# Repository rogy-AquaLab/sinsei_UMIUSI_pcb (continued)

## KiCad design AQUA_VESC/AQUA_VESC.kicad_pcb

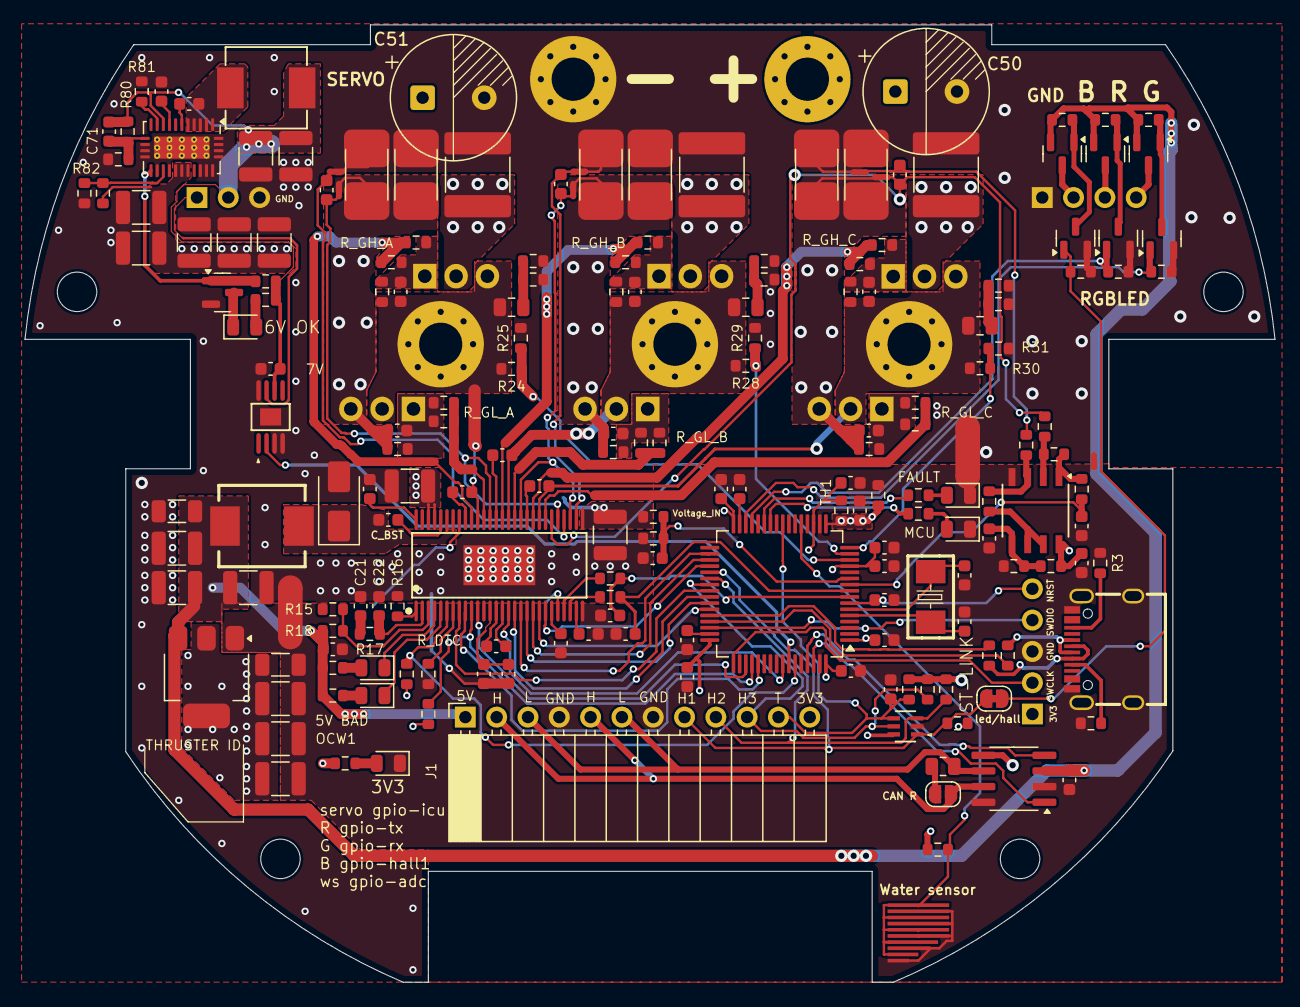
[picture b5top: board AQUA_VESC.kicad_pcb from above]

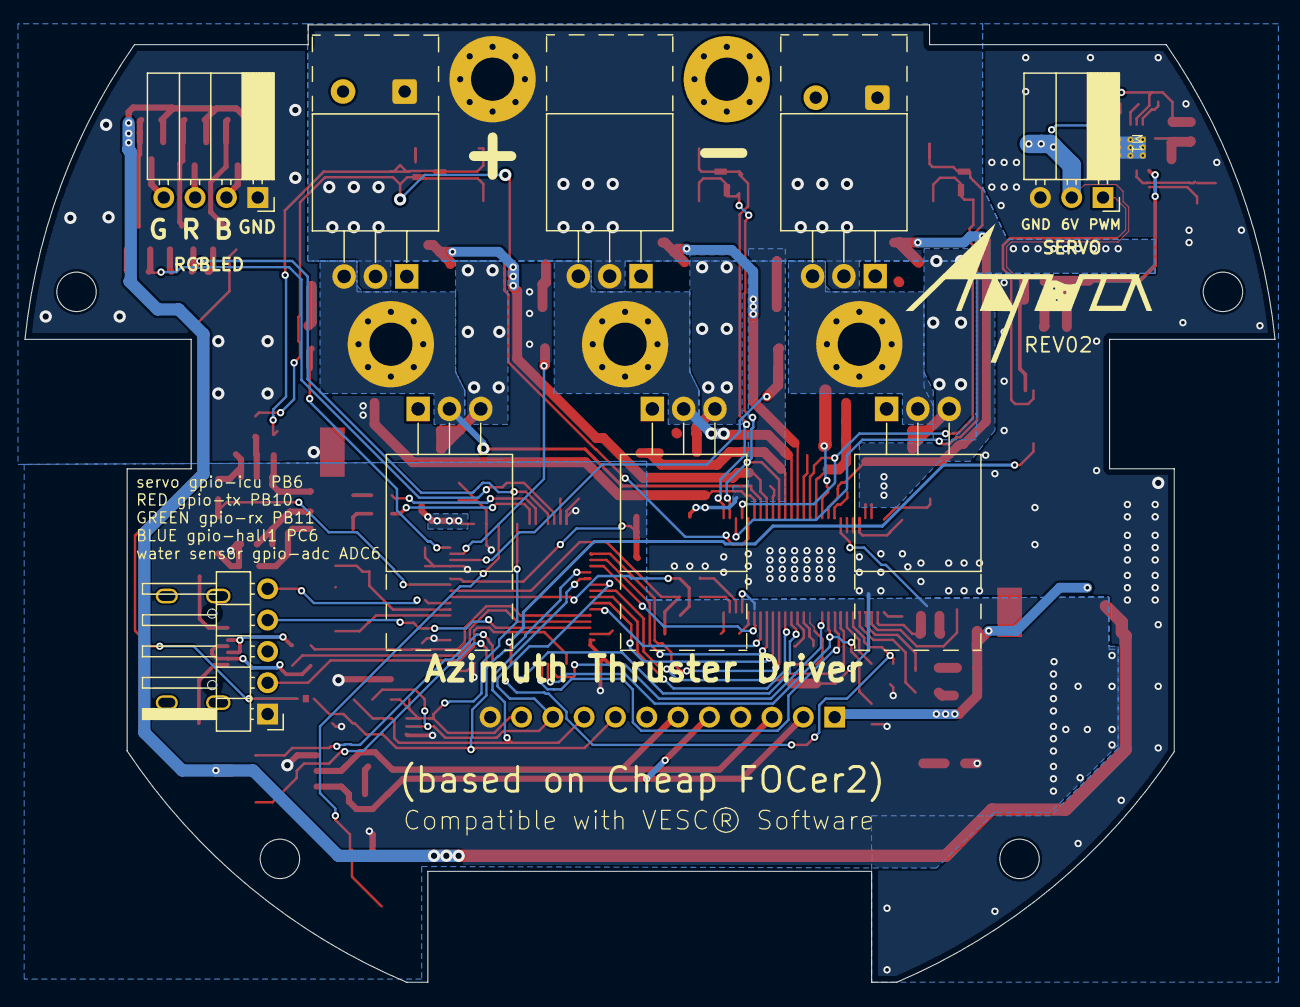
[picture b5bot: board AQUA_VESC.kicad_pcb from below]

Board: 2 copper layers, 101.4 x 77.7 mm, 213 parts (9 on the bottom side), 128 nets.

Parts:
5V1, 6V_OK1: YELLOW; LED_0805_2012Metric
C1, C2, C4, C5, C6, C7, C8, C10, C15, C16, C25, C44, C46: 100n; C_0603_1608Metric
C3: 4.7u; C_0603_1608Metric
C9, C62: 1u; C_0603_1608Metric
C11, C12: 15p; C_0603_1608Metric
C13, C14, C32, C33, C36, C41, C52, C72: 2.2u; C_0603_1608Metric
C17, C26: 2.2u; C_1206_3216Metric
C18, C19, C20, C27, C28, C29, C69, C70: 22u; C_1210_3225Metric
C21: 6.8n; C_0603_1608Metric
C22: 150p; C_0603_1608Metric
C23, C53, C54, C55, C59, C60, C61: 10n; C_0603_1608Metric
C24, C42, C63, C64, C65, C66, C67: 4.7u, 100V; C_1210_3225Metric
C30, C34, C35: 220n; C_0603_1608Metric
C31: 22n; C_0603_1608Metric
C37, C38, C39, C40, C43, C45: 1n; C_0603_1608Metric
C47, C48, C49: 10uF, 100V; C_2220_5750Metric
C50, C51: 330u; CP_Radial_D10.0mm_P5.00mm_nofill
C56, C57, C58: 4.7n, 100V; C_0805_2012Metric
C68: 0.47u; C_0603_1608Metric
C71: 12p; C_0603_1608Metric
D1: RED; LED_0805_2012Metric
D2: WHITE; LED_0805_2012Metric
D3: EMERALD; LED_0805_2012Metric
D4: SS210; D_SMA
H1, H6, H7, H8, H9: MountingHole_Pad; MountingHole_3.5mm_Pad_Via
H2, H3, H4, H5: MountingHole; MountingHole_3.2mm_M3
J1: Conn_01x12_Socket; PinSocket_1x12_P2.54mm_Horizontal
J2: Conn_01x05_Pin; PinHeader_1x05_P2.54mm_Horizontal
JP1: SolderJumper_2_Bridged; SolderJumper-2_P1.3mm_Bridged_RoundedPad1.0x1.5mm
JP2: SolderJumper_2_Open; SolderJumper-2_P1.3mm_Open_RoundedPad1.0x1.5mm
M1: Motor_Servo_Hitec; PinSocket_1x03_P2.54mm_Horizontal
NT1, NT2: NetTie_2; NetTie-2_SMD_Pad2.0mm
NT3, NT4, NT5, NT6, NT7, NT8, NT9: NetTie_2; NetTie-2_SMD_Pad0.5mm
OCW1: RED; LED_0805_2012Metric
Q1, Q2, Q3, Q4, Q5, Q6: TK3R2E06PL; TO-220-3_Horizontal_TabUp_no_hole
Q7, Q8, Q9: AO3401A; SOT-23
Q10, Q11, Q12, Q13: 2N7002; SOT-23
R1, R24, R28, R30: 39k; R_0603_1608Metric
R2, R7, R8, R9, R25, R29, R31: 2.2k; R_0603_1608Metric
R3, R6: 5.1k; R_0603_1608Metric
R4, R5: 22; R_0603_1608Metric
R10, R21, R22, R34, R37, R39, R70, R71, R72, R73, R74, R75: 10k; R_0603_1608Metric
R11, R77, R80: 100k; R_0603_1608Metric
R12, R13, R14: 100; R_0603_1608Metric
R15: 3.3k; R_0603_1608Metric
R16: 220k; R_0603_1608Metric
R17, R33, R38, R82: 20k; R_0603_1608Metric
R18: 18k; R_0603_1608Metric
R19, R20, R23, R26, R27, R32, R35, R36: 1k; R_0603_1608Metric
R40, R41, R42, R43, R44, R45, R49, R50, R51, R52, R53, R54, R55, R56, R57, R58, R59, R60: 10; R_0603_1608Metric
R46, R47, R48, R61, R62, R63: 4.7k; R_0603_1608Metric
R64, R65, R66, R67, R68, R69: 1mΩ; R_2512_Yageo_big_pads
R76: 390; R_0603_1608Metric
R78: 15k; R_0603_1608Metric
R79: 51k; R_0603_1608Metric
R81: 82k; R_0603_1608Metric
RGBLED1: Conn_01x04_Pin; PinSocket_1x04_P2.54mm_Horizontal
R_can_termination1: 120; R_0805_2012Metric
TH1: Thermistor_NTC; R_0603_1608Metric
U1: SMF05CT1G; SOT-363-6_2P2X1P35_ONS
U2: wetness sensor
U3: STM32F405RGTx; LQFP-64_10x10mm_P0.5mm
U4: TJA1051T-3; SOIC-8_3.9x4.9mm_P1.27mm
U5: AMS1117-3.3; SOT-223-3_TabPin2
U6: DRV8301QDCAQ1; HTSSOP-56_L14.0-W6.0-P0.50-LS8.0-BL
U7: 22uH; IND-SMD_L7.0-W6.6
U8: TP2604-SR; SO-8SOIC-8_TPK
U9: MX27524ES; EMSOP-8_L3.0-W3.0-P0.65-LS4.9-BL-EP
U10: 15uH; IND-SMD_L7.1-W6.6
U11: LM76002; Texas_RNP0030B_WQFN-30-1EP_4x6mm_P0.5mm_EP1.8x4.5mm_Thermal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
USB1: TYPEC; USB-C_SMD-TYPE-C-31-M-12
X1: 8MHz; CRYSTAL-SMD_L5.0-W3.2

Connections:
+3V3: C3.1, C4.1, C5.1, C6.1, C7.1, C8.1, C9.1, C17.1, C18.1, C19.1, C20.1, C44.1, J1.12, J2.1, R7.1, R8.1, R9.1, R10.1, R11.2, R14.1, R21.1, R23.1, R34.1, TH1.1, U1.6 (CATHODE), U3.1 (VBAT), U3.13 (VDDA), U3.19 (VDD), U3.32 (VDD), U3.48 (VDD), U3.64 (VDD), U4.5 (VIO), U5.2 (VO), U6.24 (REF), U6.49 (VDD_SPI), U8.8 (+VS)
+5V: C15.1, C16.1, C26.1, C27.1, C28.1, C29.1, J1.1, Q7.2 (S), Q8.2 (S), Q9.2 (S), R18.2, R19.1, R20.1, R70.2, R71.2, R72.2, U4.3 (VCC), U5.3 (VI), U7.2
+6V: C62.1, C69.1, C70.1, C71.2, M1.2 (+), R76.1, R79.1, R80.2, U9.6 (VCC), U10.2, U11.9 (BIAS)
/CAN/CANH: J1.2, J1.5, JP2.2 (B), U4.7 (CANH)
/CAN/CANL: J1.3, J1.6, R_can_termination1.2, U4.6 (CANL)
/CAN/CAN_RX: U3.61 (PB8), U4.4 (RXD)
/CAN/CAN_TX: U3.62 (PB9), U4.1 (TXD)
/DRV8301/BR_SO1: C38.1, R26.2, U3.8 (PC0)
/DRV8301/BR_SO2: C39.1, R27.2, U3.9 (PC1)
/DRV8301/BR_SO3: C43.1, R32.1, U3.10 (PC2)
/DRV8301/CS: U3.40 (PC9), U6.8 (*SCS)
/DRV8301/EN_GATE: U3.57 (PB5), U6.16 (EN_GATE)
/DRV8301/FAULT: R21.2, U3.59 (PB7), U6.6 (*FAULT)
/DRV8301/GH_A: R40.1, R43.1, U6.47 (GH_A)
/DRV8301/GH_B: R41.1, R44.1, U6.42 (GH_B)
/DRV8301/GH_C: R42.1, R45.1, U6.37 (GH_C)
/DRV8301/GL_A: R49.1, R52.1, U6.45 (GL_A)
/DRV8301/GL_B: R50.1, R53.1, U6.40 (GL_B)
/DRV8301/GL_C: R51.1, R54.1, U6.35 (GL_C)
/DRV8301/H1: U3.41 (PA8), U6.17 (INH_A)
/DRV8301/H1_LOW: C37.2, NT4.1, U6.33 (SN1), U6.44 (SL_A)
/DRV8301/H1_VS: C30.2, C53.2, C56.1, H7.1, Q1.3 (S), Q4.2 (D), R24.2, R46.2, U6.46 (SH_A)
/DRV8301/H2: U3.42 (PA9), U6.19 (INH_B)
/DRV8301/H2_LOW: C40.2, NT5.1, U6.31 (SN2), U6.39 (SL_B)
/DRV8301/H2_VS: C34.2, C54.2, C57.1, H8.1, Q2.3 (S), Q5.2 (D), R28.2, R47.2, U6.41 (SH_B)
/DRV8301/H3: U3.43 (PA10), U6.21 (INH_C)
/DRV8301/H3_LOW: C45.1, NT6.1, R35.1, U6.34 (SL_C)
/DRV8301/H3_VS: C35.2, C55.2, C58.1, H9.1, Q3.3 (S), Q6.2 (D), R30.2, R48.2, U6.36 (SH_C)
/DRV8301/L1: U3.34 (PB13), U6.18 (INL_A)
/DRV8301/L2: U3.35 (PB14), U6.20 (INL_B)
/DRV8301/L3: U3.36 (PB15), U6.22 (INL_C)
/DRV8301/SCLK: U3.51 (PC10), U6.11 (SCLK)
/DRV8301/SDI: U3.53 (PC12), U6.9 (SDI)
/DRV8301/SDO: R23.2, U3.52 (PC11), U6.10 (SDO)
/DRV8301/SENS1: R24.1, R25.1, U3.14 (PA0)
/DRV8301/SENS2: R28.1, R29.1, U3.15 (PA1)
/DRV8301/SENS3: R30.1, R31.1, U3.16 (PA2)
/DRV8301/SPA: C37.1, NT7.1, U6.32 (SP1)
/DRV8301/SPB: C40.1, NT8.1, U6.30 (SP2)
/DRV8301/SPC: C45.2, NT9.1, R36.1
/Power MOSFETs/TEMP: C52.1, R39.1, TH1.2, U3.17 (PA3)
/RGBLED_Driver/BLUE_OUT: Q9.3 (D), RGBLED1.2
/RGBLED_Driver/GREEN_GATE: Q11.1 (G), R74.1, U3.30 (PB11)
/RGBLED_Driver/GREEN_OUT: Q8.3 (D), RGBLED1.4
/RGBLED_Driver/RED_GATE: Q10.1 (G), R73.1, U3.29 (PB10)
/RGBLED_Driver/RED_OUT: Q7.3 (D), RGBLED1.3
/SERVO/SERVO_PWM: U3.58 (PB6), U9.2 (INA)
/STM32F405/ADC_EXT: R11.1, U2.1 (A), U3.21 (PA5)
/STM32F405/AN_IN: C1.1, R1.2, R2.1, U3.11 (PC3)
/STM32F405/HALL_1: J1.8, JP1.1 (A), R7.2, U1.1 (CATHODE), U3.37 (PC6)
/STM32F405/HALL_2: J1.9, R8.2, U1.3 (CATHODE), U3.38 (PC7)
/STM32F405/HALL_3: J1.10, R9.2, U1.5 (CATHODE), U3.39 (PC8)
/STM32F405/LED_GREEN: R13.1, U3.26 (PB0)
/STM32F405/LED_RED: R12.1, U3.27 (PB1)
/STM32F405/TEMP_MOTER: C2.1, J1.11, R10.2, U1.4 (CATHODE), U3.24 (PC4)
/STM32F405/USB_DM: R4.1, U3.44 (PA11)
/STM32F405/USB_DP: R5.1, U3.45 (PA12)
BLUE_GATE: JP1.2 (B), Q12.1 (G), R75.1
GNDD: C2.2, C3.2, C4.2, C5.2, C6.2, C7.2, C8.2, C9.2, C10.2, C11.2, C12.2, C13.2, C14.2, C15.2, C16.2, C17.2, C18.2, C19.2, C20.2, C36.1, C38.2, C39.2, C41.2, C43.2, C44.2, C46.2, C52.2, D1.1 (K), D2.1 (K), D3.1 (K), J1.4, J1.7, J2.3, NT1.1, NT2.1, NT3.1, R3.1, R6.2, R22.1, R37.2, R39.2, U1.2 (ANODE), U2.2 (B), U3.12 (VSSA), U3.18 (VSS), U3.60 (BOOT0), U3.63 (VSS), U4.2 (GND), U4.8 (S), U5.1 (GND), U6.28 (AGND), U8.4 (-VS), USB1.0 (SH), USB1.1 (SH), USB1.2 (SH), USB1.3 (SH), USB1.A1 (GND), USB1.A12 (GND), USB1.B1 (GND), USB1.B12 (GND)
GNDPWR: C1.2, C21.1, C22.1, C23.2, C24.2, C26.2, C27.2, C28.2, C29.2, C32.2, C33.2, C42.2, C47.2, C48.2, C49.2, C50.2, C51.2, C62.2, C63.2, C64.2, C65.2, C66.2, C67.2, C69.2, C70.2, C72.2, D4.2 (A), H6.1, M1.3 (-), NT1.2, NT2.2, NT3.2, NT7.2, NT8.2, NT9.2, Q10.2 (S), Q11.2 (S), Q12.2 (S), Q13.2 (S), R2.2, R15.1, R16.1, R25.2, R29.2, R31.2, R55.1, R56.1, R57.1, R58.1, R59.1, R60.1, R64.1, R65.1, R66.1, R67.1, R68.1, R69.1, R73.2, R74.2, R75.2, R78.2, R81.1, R82.2, RGBLED1.1, U6.57 (EPAD), U9.3 (GND), U9.4 (INB), U9.8 (ENB), U9.9 (EP), U11.13 (AGND), U11.14 (AGND), U11.15 (AGND), U11.17 (SYNC/MODE), U11.19 (NC_{GND}), U11.24 (PGND), U11.25 (PGND), U11.26 (PGND), U11.27 (NC_{GND}), U11.28 (NC_{GND}), U11.29 (NC_{GND}), U11.30 (NC_{GND}), U11.31 (AGND)
NRST: C10.1, J2.5, U3.7 (NRST)
unnamed: 5V1.2 (A), R19.2
unnamed: 5V1.1 (K), U6.4 (PWRGD)
unnamed: 6V_OK1.2 (A), R76.2
unnamed: 6V_OK1.1 (K), Q13.3 (D)
unnamed: C21.2, R17.1
unnamed: C56.2, R55.2, R56.2
unnamed: C57.2, R57.2, R58.2
unnamed: C58.2, R59.2, R60.2
unnamed: C68.2, U10.1, U11.1 (SW), U11.2 (SW), U11.3 (SW), U11.4 (SW), U11.5 (SW)
unnamed: D1.2 (A), R12.2
unnamed: D2.2 (A), R13.2
unnamed: D3.2 (A), R14.2
unnamed: C25.2, D4.1 (K), U6.50 (PH), U6.51 (PH), U7.1
unnamed: JP2.1 (A), R_can_termination1.1
unnamed: M1.1 (PWM), U9.7 (OUTA)
unnamed: OCW1.2 (A), R20.2
unnamed: OCW1.1 (K), U6.5 (*OCTW)
unnamed: C53.1, Q1.1 (G), R40.2, R43.2, R46.1
unnamed: C54.1, Q2.1 (G), R41.2, R44.2, R47.1
unnamed: C55.1, Q3.1 (G), R42.2, R45.2, R48.1
unnamed: C59.1, Q4.1 (G), R49.2, R52.2, R61.1
unnamed: C59.2, NT4.2, Q4.3 (S), R61.2, R64.2, R65.2
unnamed: C60.1, Q5.1 (G), R50.2, R53.2, R62.1
unnamed: C60.2, NT5.2, Q5.3 (S), R62.2, R66.2, R67.2
unnamed: C61.1, Q6.1 (G), R51.2, R54.2, R63.1
unnamed: C61.2, NT6.2, Q6.3 (S), R63.2, R68.2, R69.2
unnamed: Q7.1 (G), Q10.3 (D), R70.1
unnamed: Q8.1 (G), Q11.3 (D), R71.1
unnamed: Q9.1 (G), Q12.3 (D), R72.1
unnamed: Q13.1 (G), R79.2, U11.16 (PGOOD)
unnamed: C11.1, U3.5 (PH0), X1.2 (OSC2)
unnamed: C12.1, U3.6 (PH1), X1.1 (OSC1)
unnamed: C13.1, U3.31 (VCAP_1)
unnamed: C14.1, U3.47 (VCAP_2)
unnamed: C41.1, U6.27 (AVDD)
unnamed: C30.1, U6.48 (BST_A)
unnamed: C34.1, U6.43 (BST_B)
unnamed: C25.1, U6.52 (BST_BK)
unnamed: C35.1, U6.38 (BST_C)
unnamed: C22.2, R17.2, U6.2 (COMP)
unnamed: C31.2, U6.14 (CP1)
unnamed: C31.1, U6.15 (CP2)
unnamed: R22.2, U6.7 (DTC)
unnamed: C36.2, U6.23 (DVDD)
unnamed: C32.1, C33.1, U6.13 (GVDD)
unnamed: R16.2, U6.1 (RT_CLK)
unnamed: R26.1, U6.25 (SO1)
unnamed: R27.1, U6.26 (SO2)
unnamed: C23.1, U6.56 (SS_TR)
unnamed: R15.2, R18.1, U6.3 (VSENSE)
unnamed: R36.2, R38.1, U8.3 (+INA)
unnamed: C46.1, R34.2, R37.1, U8.5 (+INB)
unnamed: R33.1, R35.2, U8.2 (-INA)
unnamed: R38.2, U8.6 (-INB), U8.7 (OUTB)
unnamed: R32.2, R33.2, U8.1 (OUTA)
unnamed: C68.1, U11.6 (BOOT)
unnamed: R77.2, R78.1, U11.18 (EN)
unnamed: C71.1, R80.1, R82.1, U11.12 (FB)
unnamed: R81.2, U11.10 (RT)
unnamed: C72.1, U11.8 (VCC)
unnamed: R6.1, USB1.A5 (CC1)
unnamed: R3.2, USB1.B5 (CC2)
SWCLK: J2.2, U3.49 (PA14)
SWDIO: J2.4, U3.46 (PA13)
USB_D+: R5.2, USB1.A6 (DP1), USB1.B6 (DP2)
USB_D-: R4.2, USB1.A7 (DN1), USB1.B7 (DN2)
V_SUPPLY: C24.1, C42.1, C47.1, C48.1, C49.1, C50.1, C51.1, C63.1, C64.1, C65.1, C66.1, C67.1, H1.1, Q1.2 (D), Q2.2 (D), Q3.2 (D), R1.1, R77.1, U6.29 (PVDD1), U6.53 (PVDD2), U6.54 (PVDD2), U11.20 (PVIN), U11.21 (PVIN), U11.22 (PVIN)

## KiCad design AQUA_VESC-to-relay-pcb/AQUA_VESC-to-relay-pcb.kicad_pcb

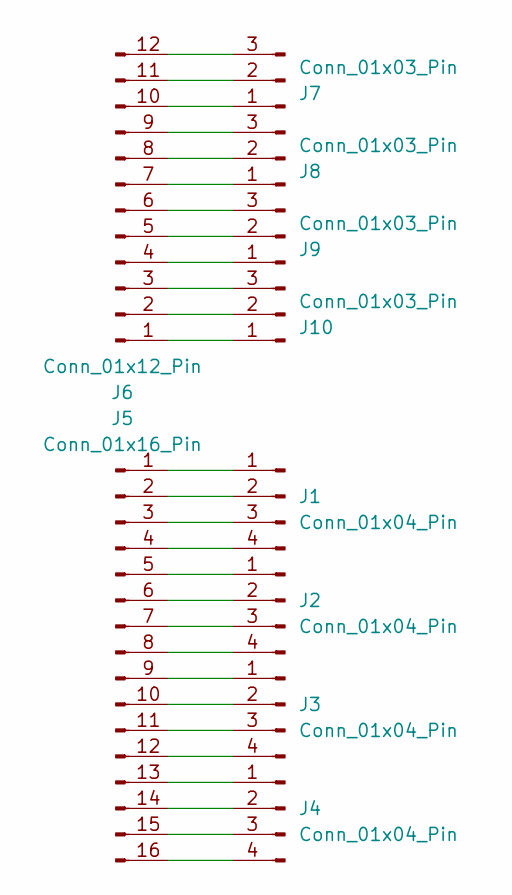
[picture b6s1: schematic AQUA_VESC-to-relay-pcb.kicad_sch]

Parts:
J1, J2, J3, J4: Conn_01x04_Pin; PinHeader_1x04_P2.54mm_Vertical
J5: Conn_01x16_Pin; PinSocket_1x16_P2.54mm_Vertical
J6: Conn_01x12_Pin; PinSocket_1x12_P2.54mm_Vertical
J7, J8, J9, J10: Conn_01x03_Pin; PinHeader_1x03_P2.54mm_Vertical

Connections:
unnamed: J1.1, J5.1
unnamed: J1.2, J5.2
unnamed: J1.3, J5.3
unnamed: J1.4, J5.4
unnamed: J2.1, J5.5
unnamed: J2.2, J5.6
unnamed: J2.3, J5.7
unnamed: J2.4, J5.8
unnamed: J3.1, J5.9
unnamed: J3.2, J5.10
unnamed: J3.3, J5.11
unnamed: J3.4, J5.12
unnamed: J4.1, J5.13
unnamed: J4.2, J5.14
unnamed: J4.3, J5.15
unnamed: J4.4, J5.16
unnamed: J6.4, J9.1
unnamed: J6.5, J9.2
unnamed: J6.6, J9.3
unnamed: J6.7, J8.1
unnamed: J6.8, J8.2
unnamed: J6.9, J8.3
unnamed: J6.10, J7.1
unnamed: J6.11, J7.2
unnamed: J6.12, J7.3
unnamed: J6.1, J10.1
unnamed: J6.2, J10.2
unnamed: J6.3, J10.3

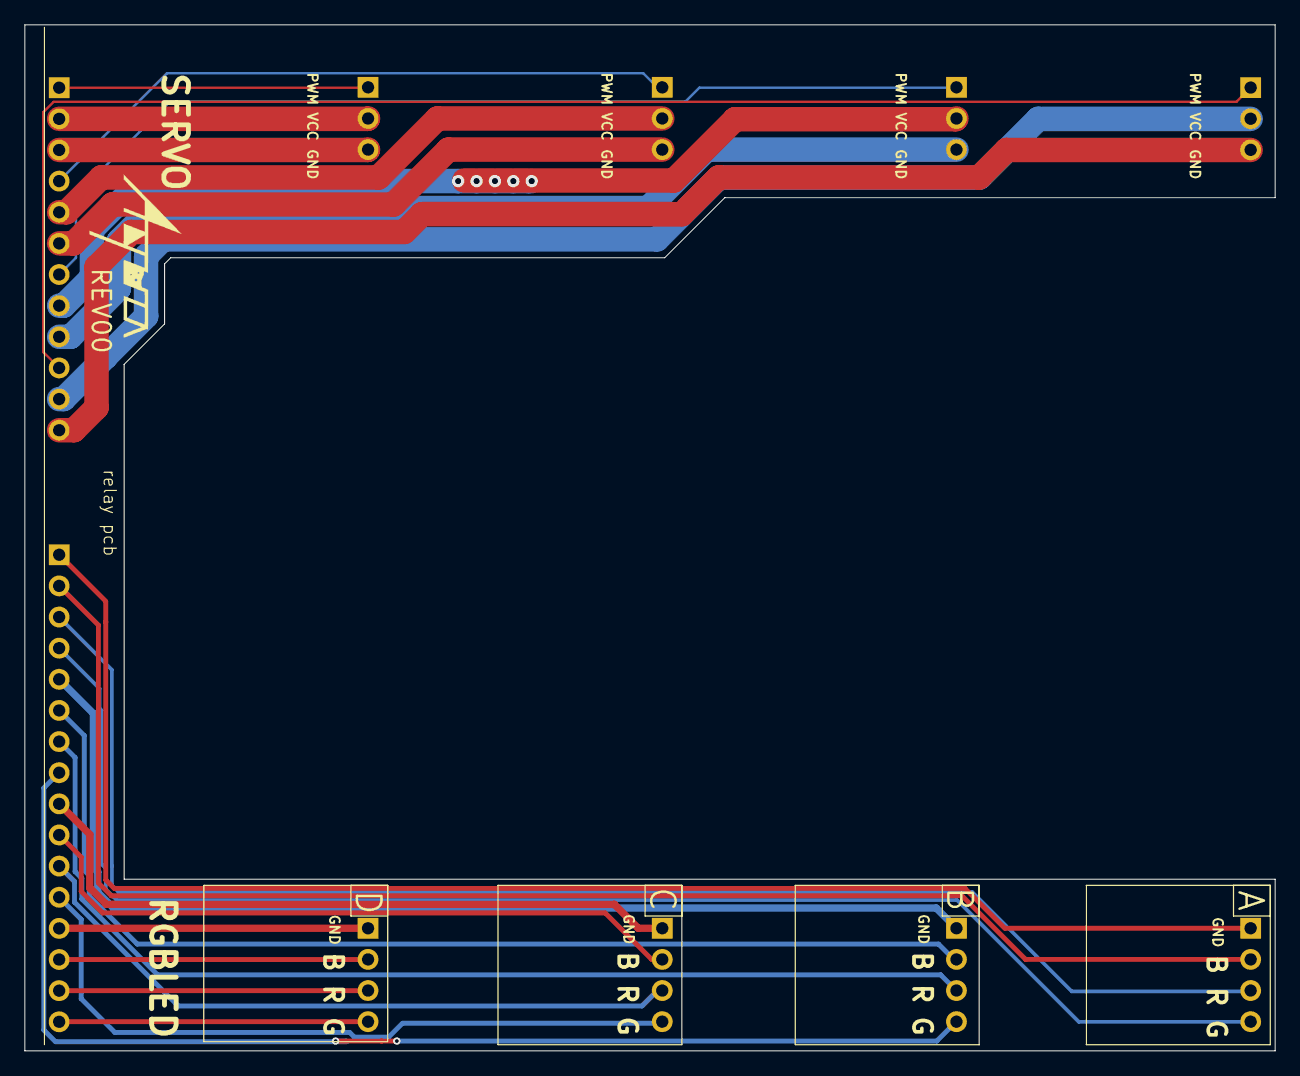
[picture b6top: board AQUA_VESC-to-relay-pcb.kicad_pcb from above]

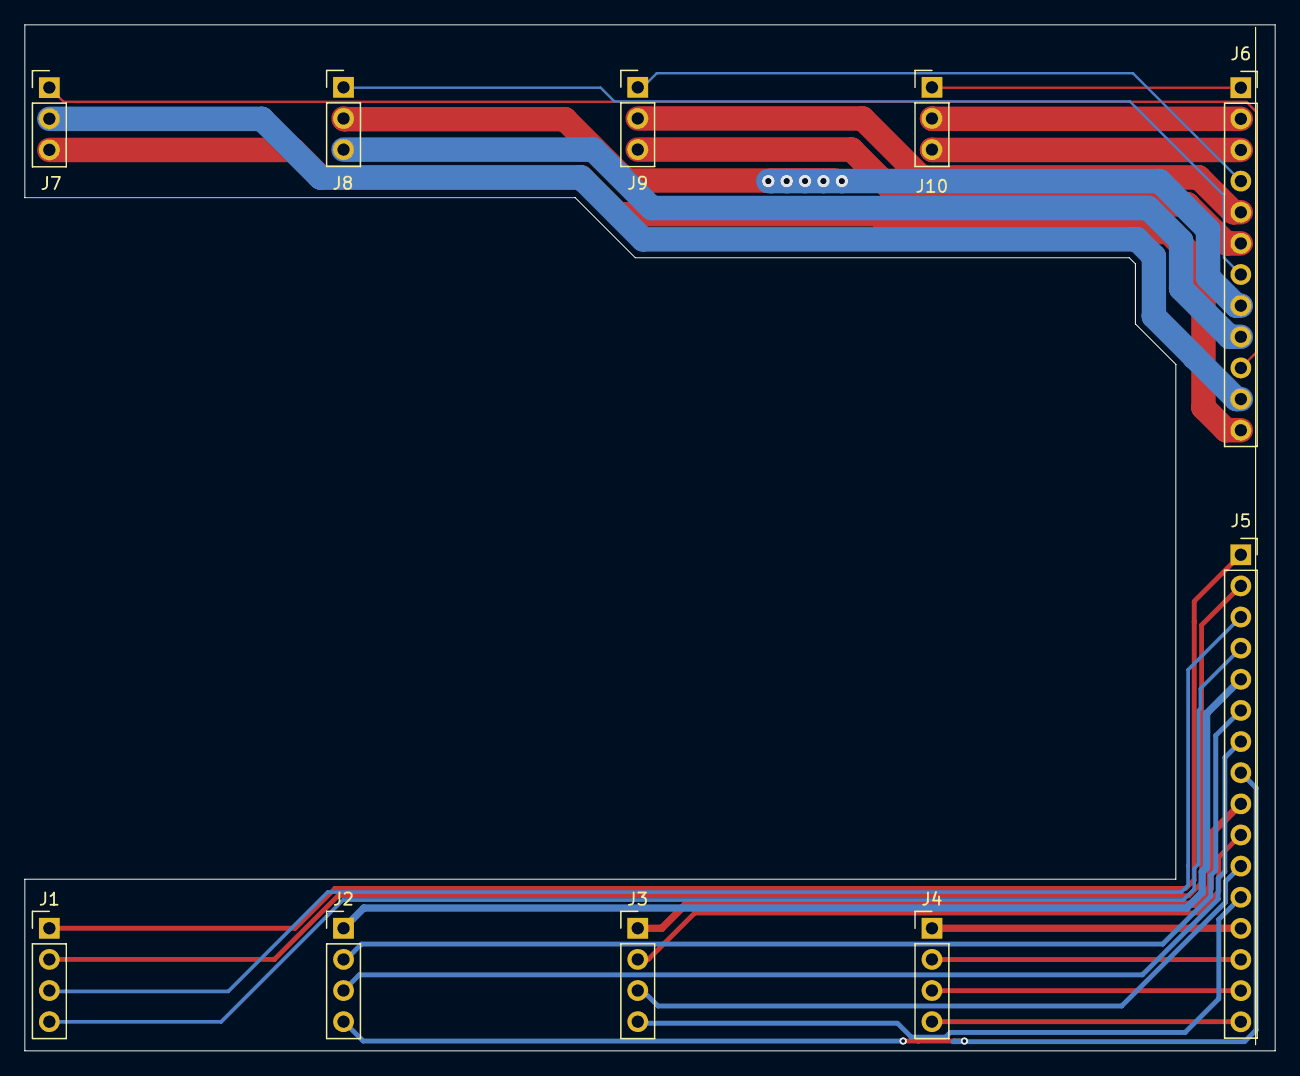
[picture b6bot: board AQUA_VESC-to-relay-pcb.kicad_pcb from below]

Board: 2 copper layers, 102.0 x 83.7 mm, 10 parts (10 on the bottom side), 28 nets.

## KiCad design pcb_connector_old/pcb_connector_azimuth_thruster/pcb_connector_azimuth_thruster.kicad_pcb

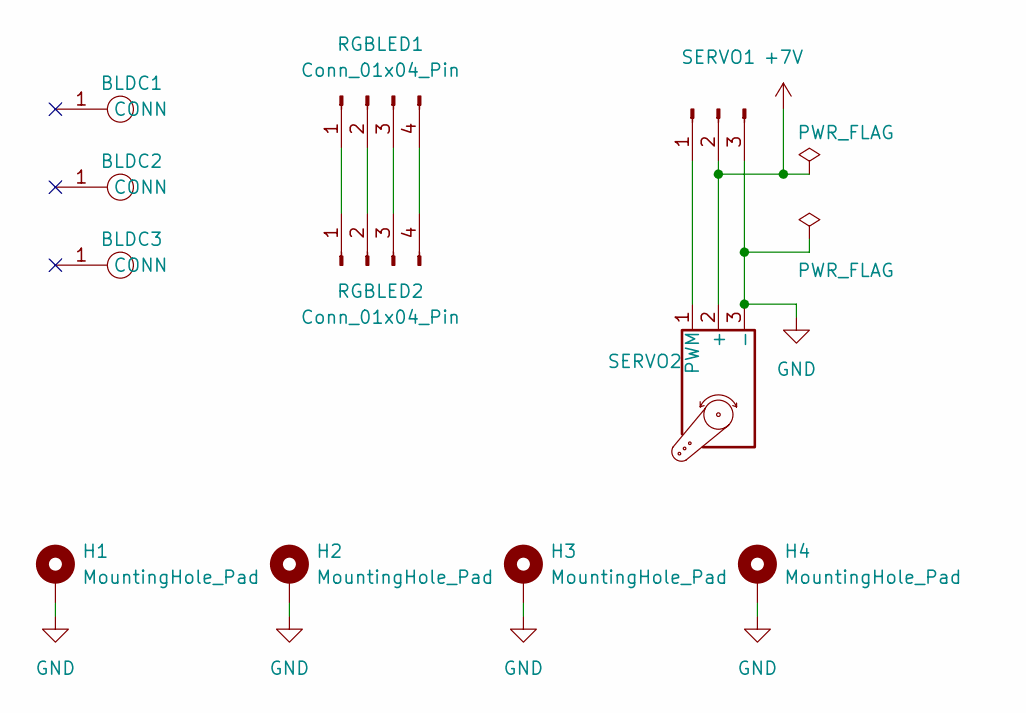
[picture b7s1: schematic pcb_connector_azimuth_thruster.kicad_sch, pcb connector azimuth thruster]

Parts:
BLDC1, BLDC2, BLDC3: bldc_connector
H1, H2, H3, H4: MountingHole_Pad; MountingHole_3.2mm_M3_large_PAD_for_spacer
RGBLED1, RGBLED2: Conn_01x04_Pin; PinHeader_1x04_P2.54mm_Vertical
SERVO1: PinSocket_1x03_P2.54mm_Vertical
SERVO2: PinHeader_1x03_P2.54mm_Vertical

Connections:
+7V: SERVO1.2, SERVO2.2 (+)
GND: H1.1, H2.1, H3.1, H4.1, SERVO1.3, SERVO2.3 (-)
unnamed: RGBLED1.1, RGBLED2.1
unnamed: RGBLED1.2, RGBLED2.2
unnamed: RGBLED1.3, RGBLED2.3
unnamed: RGBLED1.4, RGBLED2.4
unnamed: SERVO1.1, SERVO2.1 (PWM)

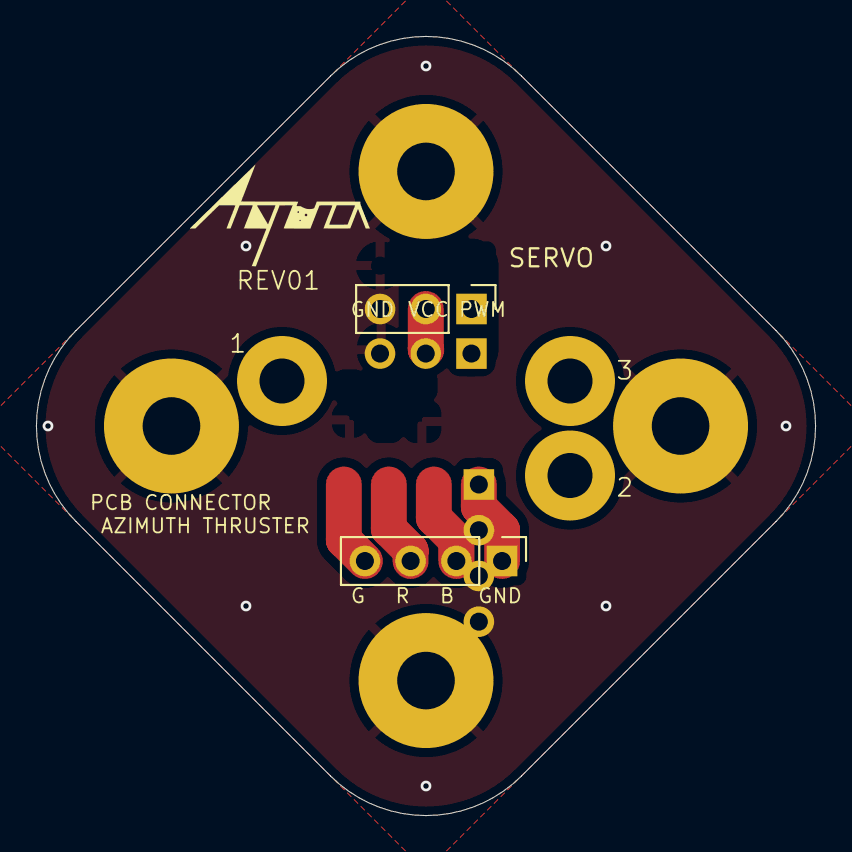
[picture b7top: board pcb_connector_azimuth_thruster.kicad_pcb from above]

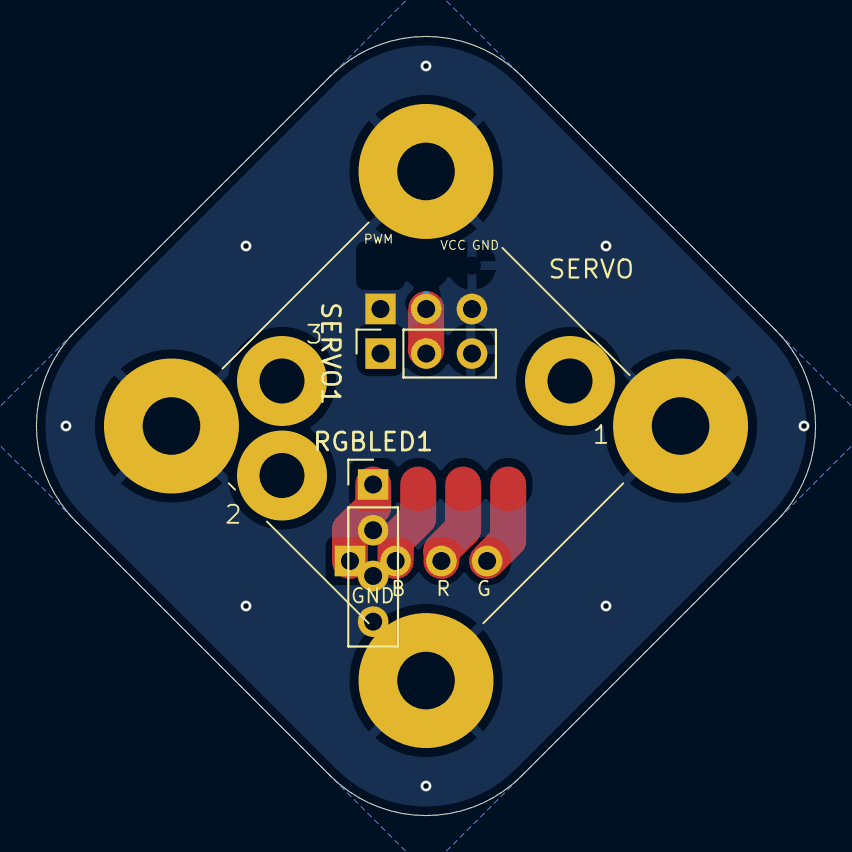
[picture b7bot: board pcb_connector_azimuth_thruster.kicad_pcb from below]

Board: 2 copper layers, 43.3 x 43.3 mm, 11 parts (2 on the bottom side), 7 nets.

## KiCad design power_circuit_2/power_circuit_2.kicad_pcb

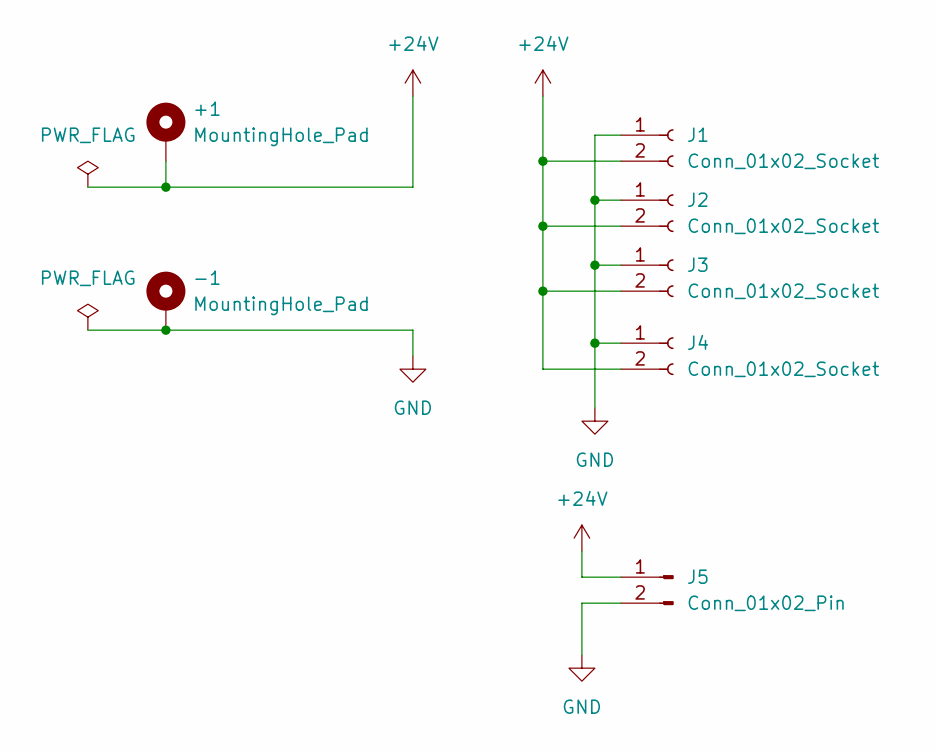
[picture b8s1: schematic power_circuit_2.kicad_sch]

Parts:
+1: MountingHole_Pad; MountingHole_3.2mm_M3_DIN965_Pad
-1: MountingHole_Pad; MountingHole_3.2mm_M3_DIN965_Pad
J1, J2, J3, J4: Conn_01x02_Socket; AMASS_XT60PW-F_1x02_P7.20mm_Horizontal
J5: Conn_01x02_Pin; JST_VH_B2PS-VH_1x02_P3.96mm_Horizontal

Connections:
+24V: +1.1, J1.2, J2.2, J3.2, J4.2, J5.1
GND: -1.1, J1.1, J2.1, J3.1, J4.1, J5.2

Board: 2 copper layers, 7 parts (4 on the bottom side), 2 nets, no tracks yet.

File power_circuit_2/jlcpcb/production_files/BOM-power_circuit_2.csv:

Comment,Designator,Footprint,LCSC,Quantity
Conn_01x02_Pin,J5,JST_VH_B2PS-VH_1x02_P3.96mm_Horizontal,,1
Conn_01x02_Socket,J4,AMASS_XT60PW-F_1x02_P7.20mm_Horizontal,,1
Conn_01x02_Socket,J3,AMASS_XT60PW-F_1x02_P7.20mm_Horizontal,,1
Conn_01x02_Socket,J1,AMASS_XT60PW-F_1x02_P7.20mm_Horizontal,,1
Conn_01x02_Socket,J2,AMASS_XT60PW-F_1x02_P7.20mm_Horizontal,,1

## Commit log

2025-04-14 DCDCコンバーター設計開始
2025-04-15 ファイル追加
2025-04-16 DCDCコンバーター設計完了
2025-04-20 入力コンデンサ、出力コンデンサを直した
2025-04-20 LEDドライバのデータシート追加
2025-04-26 若干修正
2025-04-26 テスト基盤回路図作成、基板作成中
2025-04-28 LM25145テスト基板完成、実験用レポートひな形準備
2025-04-28 スラスターLED用基板を追加
2025-04-28 gitignoreを追加
2025-04-28 不要なファイルを削除
2025-04-29 LM25145_testの基板サイズを小さくして、発注
2025-05-09 OKL[200~過渡応答を
2025-05-12 制御基板配線開始
2025-05-18 制御基板PCB7割完成
2025-05-20 配線完了
2025-05-22 control_unit Rev00発注
2025-05-28 制御基板のファイル整理と微調整
2025-06-03 基板防水(LAN)作成開始
2025-06-10 gitignoreにOSが自動生成する不要ファイルを追加
2025-06-10 スラスターLED用基板を修正
2025-06-10 started creating headlight_upper_side
2025-06-10 modified
2025-07-05 基板防水REV00発注完了
2025-07-05 ヘッドライト基盤REV01作成
2025-07-21 VESC7割
2025-07-24 AQUA VESC仮完成
2025-07-28 VESC発注
2025-07-31 スラスタLED基盤 REV02作成
2025-08-18 AQUA_VESC REV01作成
2025-08-26 旧基板防水をpcb_connector_oldに移動
2025-09-15 制御基板REV01完成
2025-09-19 方針変更、back_connector_escにMT60を使用しないことに
2025-10-03 ESC周りの配線用基板進捗
